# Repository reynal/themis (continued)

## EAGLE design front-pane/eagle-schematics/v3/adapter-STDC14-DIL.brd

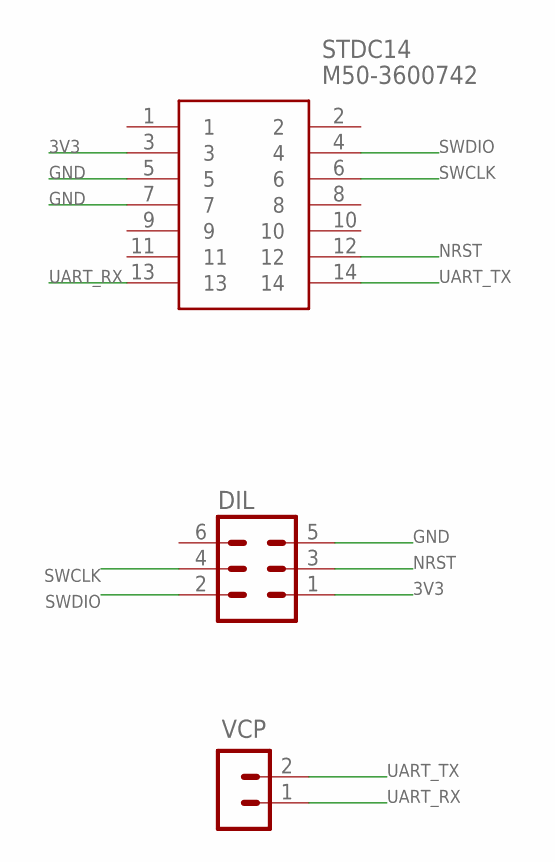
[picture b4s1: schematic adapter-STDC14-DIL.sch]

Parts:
DIL: MA03-2
STDC14: M50-3600742
VCP: MA02-1

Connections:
3V3: DIL.1, STDC14.3
GND: DIL.5, STDC14.5, STDC14.7
NRST: DIL.3, STDC14.12
SWCLK: DIL.4, STDC14.6
SWDIO: DIL.2, STDC14.4
UART_RX: STDC14.13, VCP.1
UART_TX: STDC14.14, VCP.2

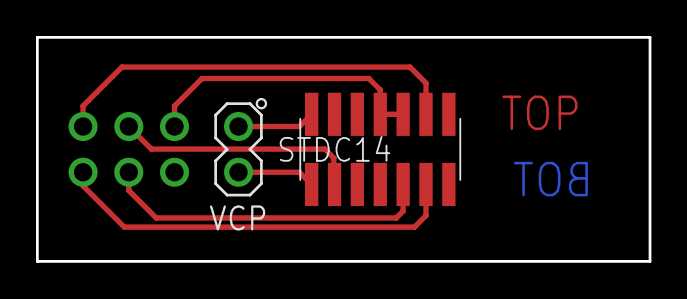
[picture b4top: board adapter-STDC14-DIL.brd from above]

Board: 2 copper layers, 34.0 x 12.4 mm, 3 parts (1 on the bottom side), 7 nets.

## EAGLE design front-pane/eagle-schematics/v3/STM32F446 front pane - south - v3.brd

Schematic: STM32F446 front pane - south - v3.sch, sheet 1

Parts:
C1, C4: 100n; 0805-CAP
C2, C3: 10u; CPOL2917
C5, C6, C7, C8, C9, C10, C11, C12, C13, C14, C20, C21, C22, C23, C24, C25, C26, C27, C28, C29, C34, C35, C36, C37, C38, C39, C40, C41, C42, C43, C44: 10n; 0805-CAP
C15, C16, C17, C18, C19, C30, C31, C32, C33, C45, C46, C47, C48: 100n; 1206
CON_NORTH_BRD: MA10-2
D1, D2, D3, D4: CZXR-80RGB03-A; LED4-2.0-D8.0MM
IC1, IC2, IC3, IC4, IC5, IC6, IC7, IC8, IC9, IC10, IC11, IC12, IC13: NEOPIXEL-TLC59731DR; SOIC127P600X175-8N
MCP_000, MCP_001: MCP23017; SOIC-28
R1, R2, R3, R4: 1k; R0805
R5, R6, R7, R8, R9, R10, R11, R12, R13, R14, R30, R31, R32, R33, R34, R35, R36, R37, R38, R39, R55, R56, R57, R58, R59, R60, R61, R62, R63, R64, R65: 470; 1206
R15, R16, R17, R19, R20, R21, R23, R24, R25, R27, R28, R29, R40, R41, R42, R44, R45, R46, R48, R49, R50, R52, R53, R54, R66, R67, R68, R70, R71, R72, R74, R75, R76, R78, R79, R80, R81, R82, R83: 100; 1206
R18, R22, R26, R43, R47, R51, R69, R73, R77: 10k; 1206
S1, S2, S3, S4, S5, S6, S7, S8, S9: ENCODER-RGB-SWITCH-NO_NUT; ENCODER_LED_3
SW1, SW2, SW3, SW4: B3F-1000

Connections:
3V3: C1.1, C2.+, C3.+, C4.1, C15.1, C16.1, C17.1, C18.1, C19.1, C30.1, C31.1, C32.1, C33.1, C45.1, C46.1, C47.1, C48.1, CON_NORTH_BRD.2, CON_NORTH_BRD.4, D1.2 (+), D2.2 (+), D3.2 (+), D4.2 (+), IC1.8 (VCC), IC2.8 (VCC), IC3.8 (VCC), IC4.8 (VCC), IC5.8 (VCC), IC6.8 (VCC), IC7.8 (VCC), IC8.8 (VCC), IC9.8 (VCC), IC10.8 (VCC), IC11.8 (VCC), IC12.8 (VCC), IC13.8 (VCC), MCP_000.9 (VDD), MCP_001.9 (VDD), MCP_001.15 (A0), R1.2, R2.2, R3.2, R4.2, S1.5 (+), S2.5 (+), S3.5 (+), S4.5 (+), S5.5 (+), S6.5 (+), S7.5 (+), S8.5 (+), S9.5 (+); also elsewhere on the board
DATA_PIXEL11: IC4.5 (SDO), IC8.6 (SDI)
DATA_PIXEL12: IC1.5 (SDO), IC4.6 (SDI)
DATA_PIXEL13: IC1.6 (SDI), IC3.5 (SDO)
DATA_PIXEL14: IC2.5 (SDO), IC3.6 (SDI)
DATA_PIXEL21: IC7.6 (SDI), IC8.5 (SDO)
DATA_PIXEL22: IC6.6 (SDI), IC7.5 (SDO)
DATA_PIXEL23: IC5.6 (SDI), IC6.5 (SDO)
DATA_PIXEL24: IC5.5 (SDO), IC9.6 (SDI)
DATA_PIXEL32: IC12.5 (SDO), IC13.6 (SDI)
DATA_PIXEL33: IC11.5 (SDO), IC12.6 (SDI)
DATA_PIXEL34: IC10.5 (SDO), IC11.6 (SDI)
DATA_PIXEL35: IC9.5 (SDO), IC10.6 (SDI)
GND: C1.2, C2.-, C3.-, C4.2, C5.1, C6.1, C7.1, C8.1, C9.1, C10.1, C11.1, C12.2, C13.2, C14.2, C15.2, C16.2, C17.2, C18.2, C19.2, C20.1, C21.1, C22.1, C23.1, C24.1, C25.1, C26.1, C27.2, C28.2, C29.2, C30.2, C31.2, C32.2, C33.2, C34.1, C35.1, C36.1, C37.1, C38.1, C39.1, C40.1, C41.1, C42.2, C43.2, C44.2, C45.2, C46.2, C47.2, C48.2, CON_NORTH_BRD.1, IC1.4 (GND), IC2.4 (GND), IC3.4 (GND), IC4.4 (GND), IC5.4 (GND), IC6.4 (GND), IC7.4 (GND), IC8.4 (GND), IC9.4 (GND), IC10.4 (GND), IC11.4 (GND), IC12.4 (GND), IC13.4 (GND), MCP_000.10 (VSS), MCP_000.15 (A0), MCP_000.16 (A1), MCP_000.17 (A2), MCP_001.10 (VSS), MCP_001.16 (A1), MCP_001.17 (A2), R18.2, R22.2, R26.2, R43.2, R47.2, R51.2, R69.2, R73.2, R77.2, S1.C, S2.C, S3.C, S4.C, S5.C, S6.C, S7.C, S8.C, S9.C, SW1.1, SW1.2, SW2.1, SW2.2, SW3.1, SW3.2, SW4.1, SW4.2; also elsewhere on the board
GPA0_11: MCP_000.21 (GPA0), R32.1, S4.B
GPA0_12: MCP_001.21 (GPA0), R58.1, S7.B
GPA1_11: MCP_000.22 (GPA1), R31.1, S4.A
GPA1_12: MCP_001.22 (GPA1), R63.1, R69.1, S7.3 (SW)
GPA2_11: MCP_000.23 (GPA2), R37.1, R43.1, S4.3 (SW)
GPA2_12: MCP_001.23 (GPA2), R57.1, S7.A
GPA3_11: MCP_000.24 (GPA3), R33.1, S5.A
GPA3_12: MCP_001.24 (GPA3), R60.1, S8.B
GPA4_11: MCP_000.25 (GPA4), R34.1, S5.B
GPA4_12: MCP_001.25 (GPA4), R59.1, S8.A
GPA5_11: MCP_000.26 (GPA5), R38.1, R47.1, S5.3 (SW)
GPA5_12: MCP_001.26 (GPA5), R64.1, R73.1, S8.3 (SW)
GPA6_11: MCP_000.27 (GPA6), R14.1, R26.1, S3.3 (SW)
GPA6_12: MCP_001.27 (GPA6), R55.1, SW3.3, SW3.4
GPA7_11: MCP_000.28 (GPA7), R5.1, SW1.3, SW1.4
GPA7_12: MCP_001.28 (GPA7), R56.1, SW4.3, SW4.4
GPB0_11: MCP_000.1 (GPB0), R10.1, S3.A
GPB1_11: MCP_000.2 (GPB1), R11.1, S3.B
GPB1_12: MCP_001.2 (GPB1), R62.1, S9.B
GPB2_11: MCP_000.3 (GPB2), R8.1, S2.A
GPB2_12: MCP_001.3 (GPB2), R65.1, R77.1, S9.3 (SW)
GPB3_11: MCP_000.4 (GPB3), R9.1, S2.B
GPB3_12: MCP_001.4 (GPB3), R61.1, S9.A
GPB4_11: MCP_000.5 (GPB4), R13.1, R22.1, S2.3 (SW)
GPB4_12: MCP_001.5 (GPB4), R39.1, R51.1, S6.3 (SW)
GPB5_11: MCP_000.6 (GPB5), R12.1, R18.1, S1.3 (SW)
GPB5_12: MCP_001.6 (GPB5), R35.1, S6.A
GPB6_11: MCP_000.7 (GPB6), R6.1, S1.A
GPB6_12: MCP_001.7 (GPB6), R36.1, S6.B
GPB7_11: MCP_000.8 (GPB7), R7.1, S1.B
GPB7_12: MCP_001.8 (GPB7), R30.1, SW2.3, SW2.4
I2C2_SCL: CON_NORTH_BRD.20; also elsewhere on the board
I2C2_SDA: CON_NORTH_BRD.5; also elsewhere on the board
I2C3_SCL: CON_NORTH_BRD.12, MCP_000.12 (SCL), MCP_001.12 (SCL), R2.1, R4.1
I2C3_SDA: CON_NORTH_BRD.11, MCP_000.13 (SDA), MCP_001.13 (SDA), R1.1, R3.1
INTA_2: CON_NORTH_BRD.13; also elsewhere on the board
INTA_11: CON_NORTH_BRD.8, MCP_000.20 (INTA)
INTA_12: CON_NORTH_BRD.9, MCP_001.20 (INTA)
INTA_31: CON_NORTH_BRD.18; also elsewhere on the board
INTA_32: CON_NORTH_BRD.15; also elsewhere on the board
INTB_2: CON_NORTH_BRD.14; also elsewhere on the board
INTB_11: CON_NORTH_BRD.7, MCP_000.19 (INTB)
INTB_12: CON_NORTH_BRD.10, MCP_001.19 (INTB)
INTB_31: CON_NORTH_BRD.17; also elsewhere on the board
INTB_32: CON_NORTH_BRD.16; also elsewhere on the board
unnamed: IC12.1 (OUT0), R81.1
unnamed: IC12.2 (OUT1), R82.1
unnamed: R23.2, S3.1 (-R)
unnamed: R24.2, S3.2 (-G)
unnamed: R25.2, S3.4 (-B)
unnamed: IC4.1 (OUT0), R23.1
unnamed: IC4.2 (OUT1), R24.1
unnamed: IC4.3 (OUT2), R25.1
unnamed: C10.2, R10.2
unnamed: C11.2, R11.2
unnamed: C14.1, R14.2
unnamed: R19.2, S2.1 (-R)
unnamed: R20.2, S2.2 (-G)
unnamed: R21.2, S2.4 (-B)
unnamed: IC3.1 (OUT0), R19.1
unnamed: IC3.2 (OUT1), R20.1
unnamed: IC3.3 (OUT2), R21.1
unnamed: C8.2, R8.2
unnamed: C9.2, R9.2
unnamed: C13.1, R13.2
unnamed: R15.2, S1.1 (-R)
unnamed: R16.2, S1.2 (-G)
unnamed: R17.2, S1.4 (-B)
unnamed: IC2.1 (OUT0), R15.1
unnamed: IC2.2 (OUT1), R16.1
unnamed: IC2.3 (OUT2), R17.1
unnamed: C6.2, R6.2
unnamed: C7.2, R7.2
unnamed: C12.1, R12.2
unnamed: IC12.3 (OUT2), R83.1
unnamed: C35.2, R56.2
unnamed: D4.1 (R), R83.2
unnamed: D4.4 (B), R82.2
unnamed: D4.3 (G), R81.2
unnamed: IC1.1 (OUT0), R27.1
unnamed: IC1.2 (OUT1), R28.1
unnamed: IC1.3 (OUT2), R29.1
unnamed: C5.2, R5.2
unnamed: R48.2, S6.1 (-R)
unnamed: R49.2, S6.2 (-G)
unnamed: R50.2, S6.4 (-B)
unnamed: IC8.1 (OUT0), R48.1
unnamed: IC8.2 (OUT1), R49.1
unnamed: IC8.3 (OUT2), R50.1
unnamed: C25.2, R35.2
unnamed: C26.2, R36.2
unnamed: C29.1, R39.2
unnamed: D1.1 (R), R29.2
unnamed: D1.4 (B), R28.2
unnamed: D1.3 (G), R27.2
unnamed: R44.2, S5.1 (-R)
unnamed: R45.2, S5.2 (-G)
unnamed: R46.2, S5.4 (-B)
unnamed: IC6.1 (OUT0), R44.1
unnamed: IC6.2 (OUT1), R45.1
unnamed: IC6.3 (OUT2), R46.1
unnamed: C23.2, R33.2
unnamed: C24.2, R34.2
unnamed: C28.1, R38.2
unnamed: IC7.1 (OUT0), R52.1
unnamed: IC7.2 (OUT1), R53.1
unnamed: IC7.3 (OUT2), R54.1
unnamed: C20.2, R30.2
unnamed: D2.1 (R), R54.2
unnamed: D2.4 (B), R53.2
unnamed: D2.3 (G), R52.2
unnamed: R40.2, S4.1 (-R)
unnamed: R41.2, S4.2 (-G)
unnamed: R42.2, S4.4 (-B)
unnamed: IC5.1 (OUT0), R40.1
unnamed: IC5.2 (OUT1), R41.1
unnamed: IC5.3 (OUT2), R42.1
unnamed: C21.2, R31.2
unnamed: C22.2, R32.2
unnamed: C27.1, R37.2
unnamed: R74.2, S9.1 (-R)
unnamed: R75.2, S9.2 (-G)
unnamed: R76.2, S9.4 (-B)
unnamed: IC13.1 (OUT0), R74.1
unnamed: IC13.2 (OUT1), R75.1
unnamed: IC13.3 (OUT2), R76.1
unnamed: C40.2, R61.2
unnamed: C41.2, R62.2
unnamed: C44.1, R65.2
unnamed: IC11.1 (OUT0), R78.1
unnamed: IC11.2 (OUT1), R79.1
unnamed: IC11.3 (OUT2), R80.1
unnamed: C34.2, R55.2
unnamed: D3.1 (R), R80.2
unnamed: D3.4 (B), R79.2
unnamed: D3.3 (G), R78.2
unnamed: R70.2, S8.1 (-R)
unnamed: R71.2, S8.2 (-G)
unnamed: R72.2, S8.4 (-B)
unnamed: IC10.1 (OUT0), R70.1
unnamed: IC10.2 (OUT1), R71.1
unnamed: IC10.3 (OUT2), R72.1
unnamed: C38.2, R59.2
unnamed: C39.2, R60.2
unnamed: C43.1, R64.2
unnamed: R66.2, S7.1 (-R)
unnamed: R67.2, S7.2 (-G)
unnamed: R68.2, S7.4 (-B)
unnamed: IC9.1 (OUT0), R66.1
unnamed: IC9.2 (OUT1), R67.1
unnamed: IC9.3 (OUT2), R68.1
unnamed: C36.2, R57.2
unnamed: C37.2, R58.2
unnamed: C42.1, R63.2
PIXEL42: IC2.6 (SDI); also elsewhere on the board
RST: CON_NORTH_BRD.3, MCP_000.18 (!RESET), MCP_001.18 (!RESET); also elsewhere on the board
SPI1_MOSI: CON_NORTH_BRD.6; also elsewhere on the board
SPI3_MOSI: CON_NORTH_BRD.19; also elsewhere on the board

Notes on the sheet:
RGB ENCODER 11
RGB ENCODER 13
RGB ENCODER 14
RGB ENCODER 21
RGB ENCODER 23
RGB ENCODER 24
RGB ENCODER 31
RGB ENCODER 34
RGB ENCODER 35
OSCILLATORS
SWITCH RGB 12
SWITCH RGB 22
SWITCH RGB 33
SWITCH RGB 32
MCP 11 & 12

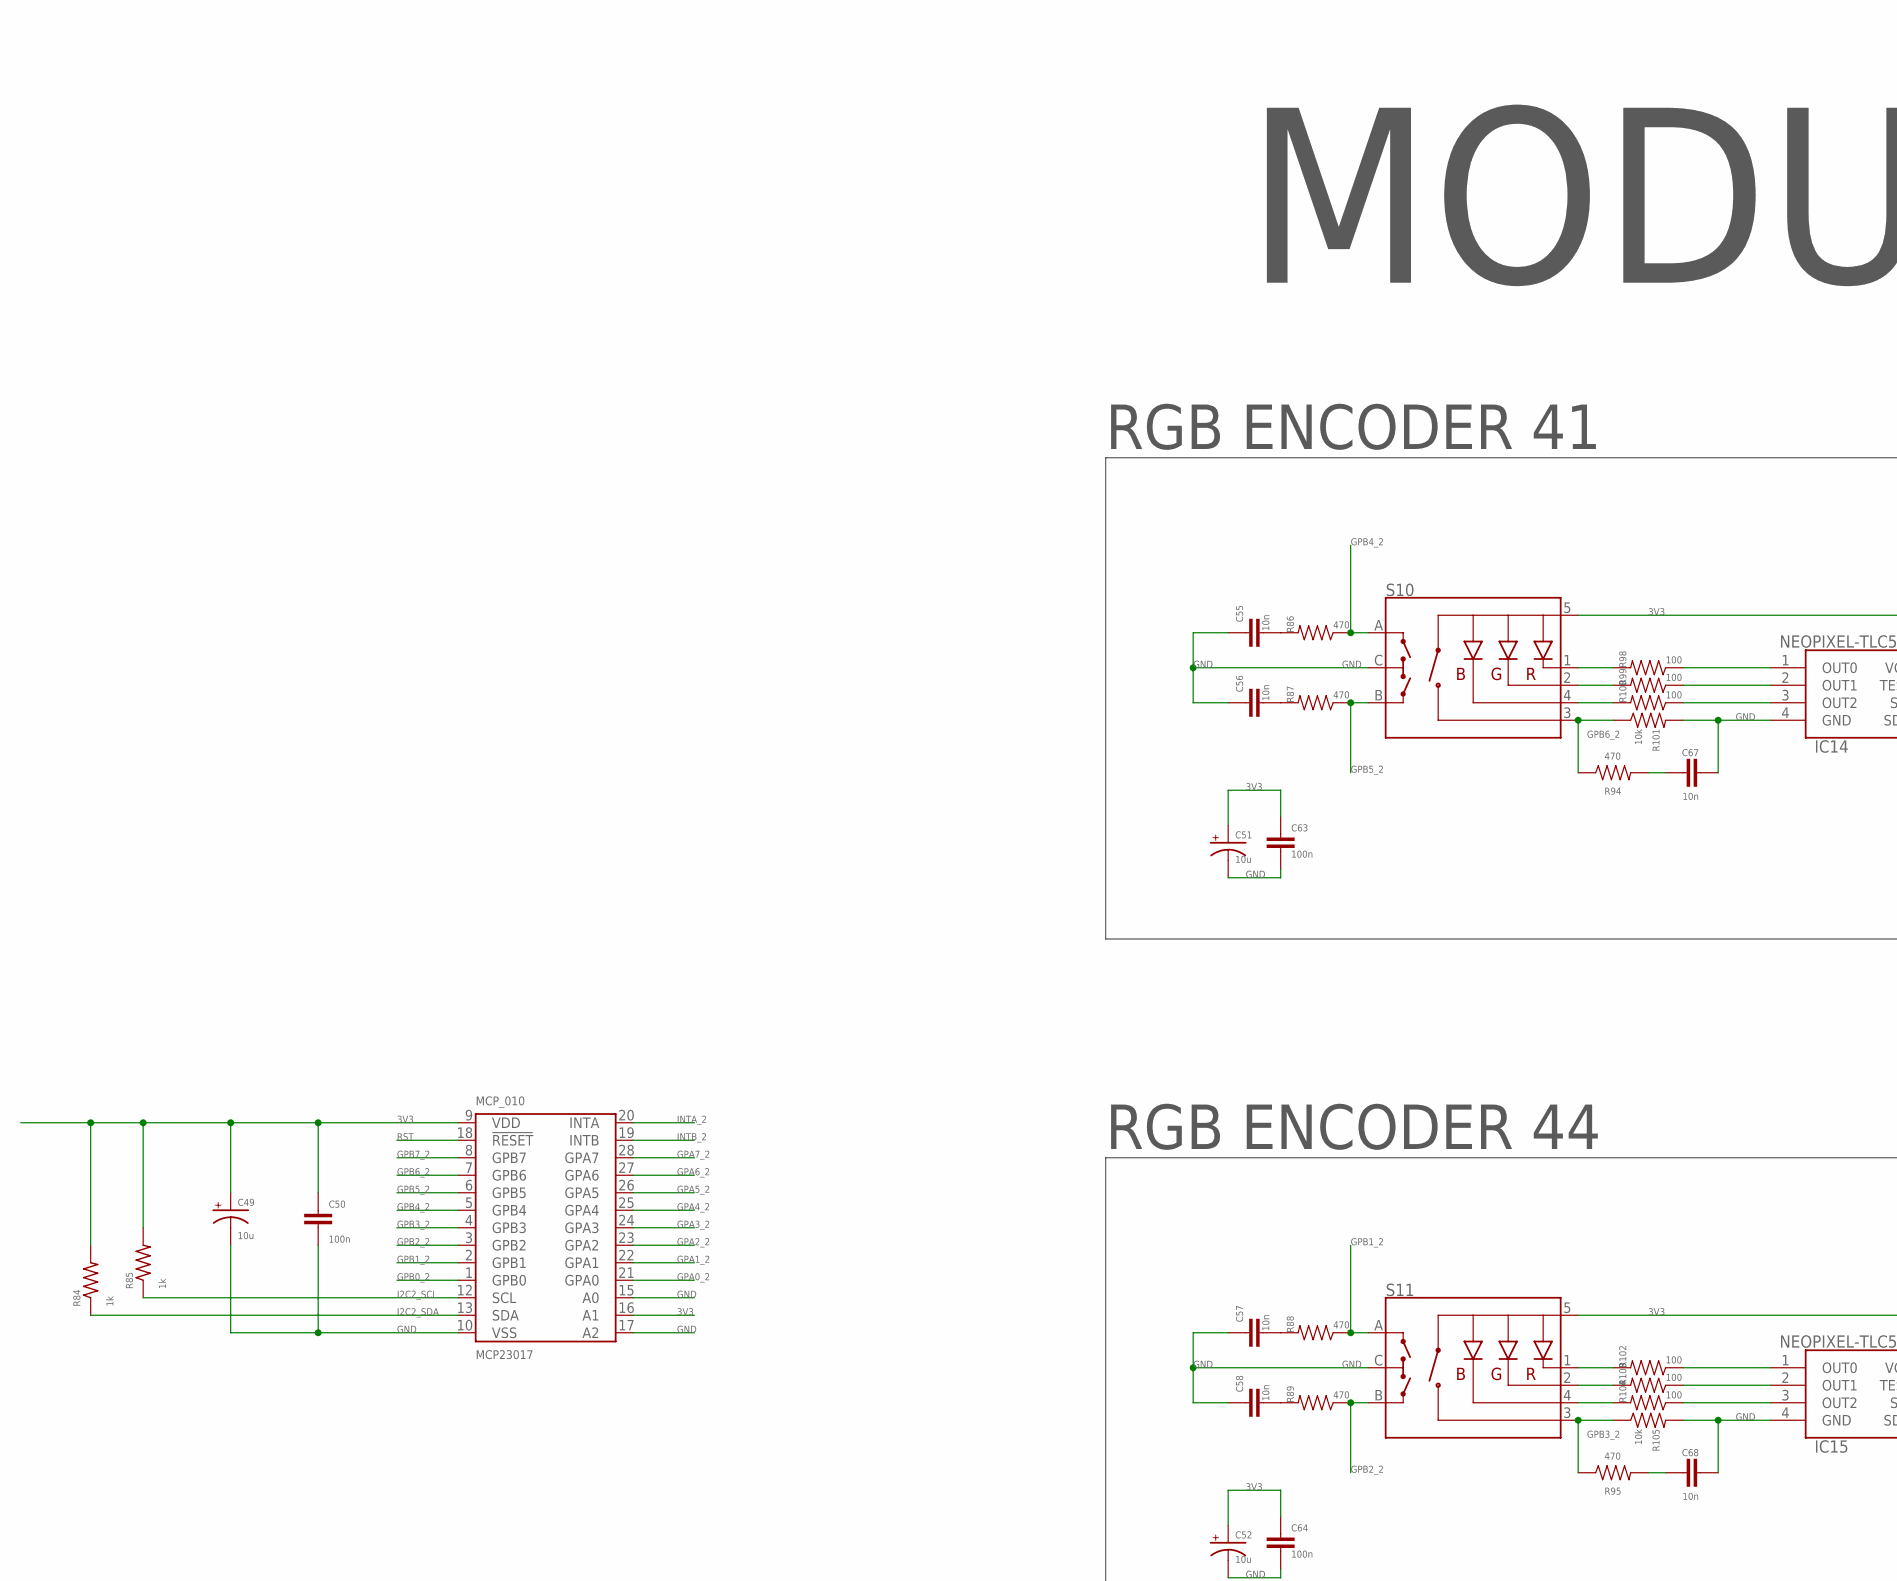
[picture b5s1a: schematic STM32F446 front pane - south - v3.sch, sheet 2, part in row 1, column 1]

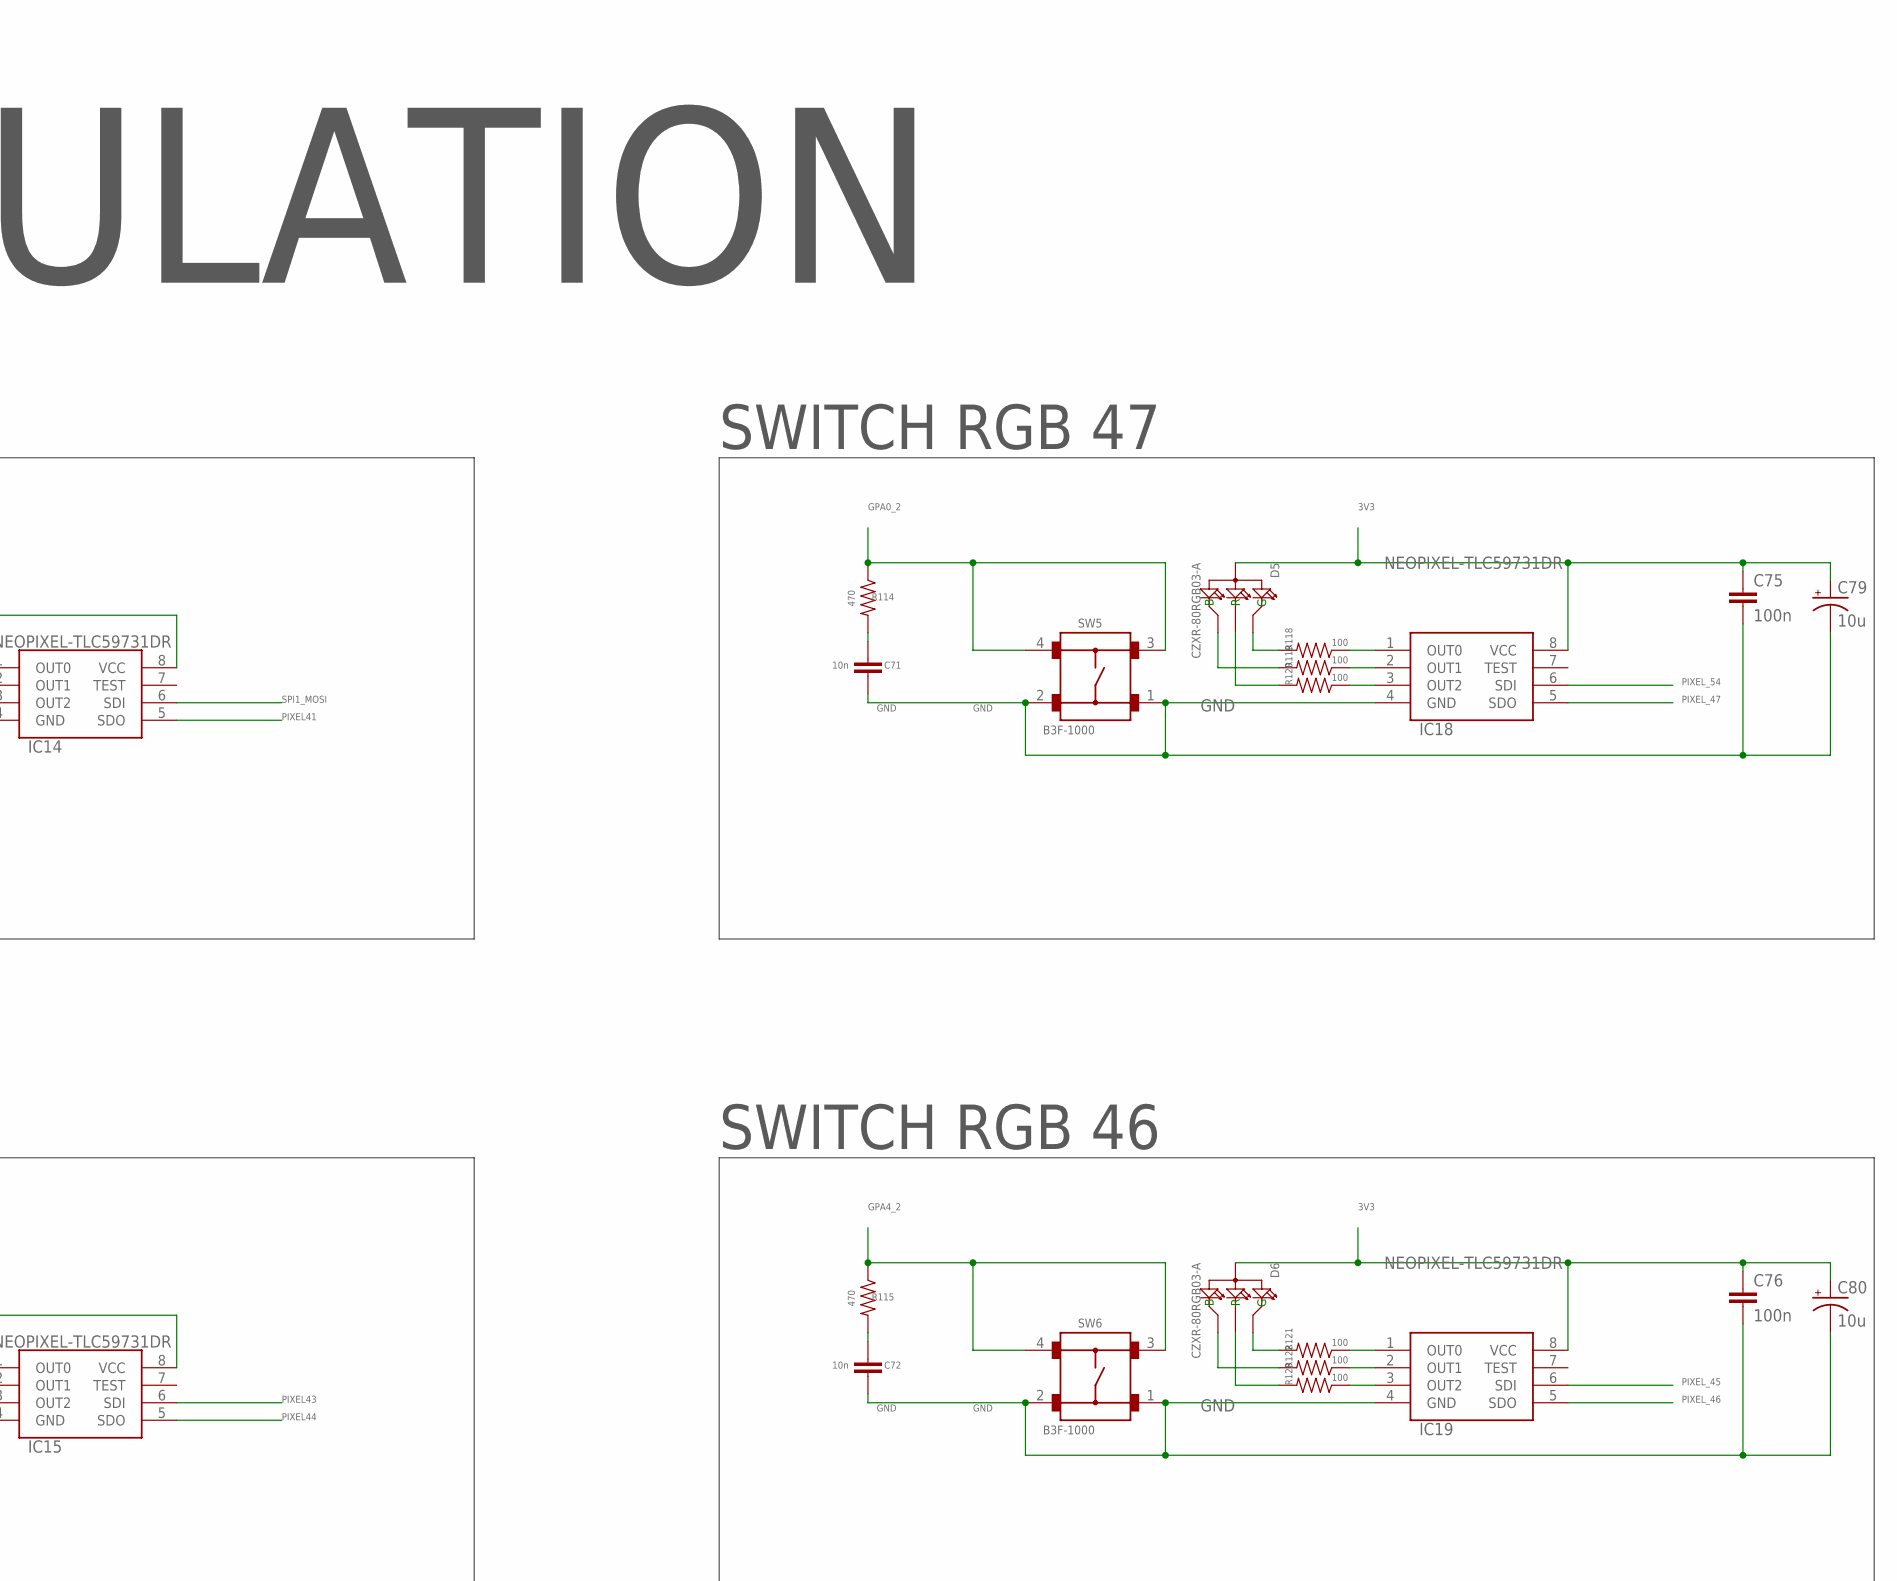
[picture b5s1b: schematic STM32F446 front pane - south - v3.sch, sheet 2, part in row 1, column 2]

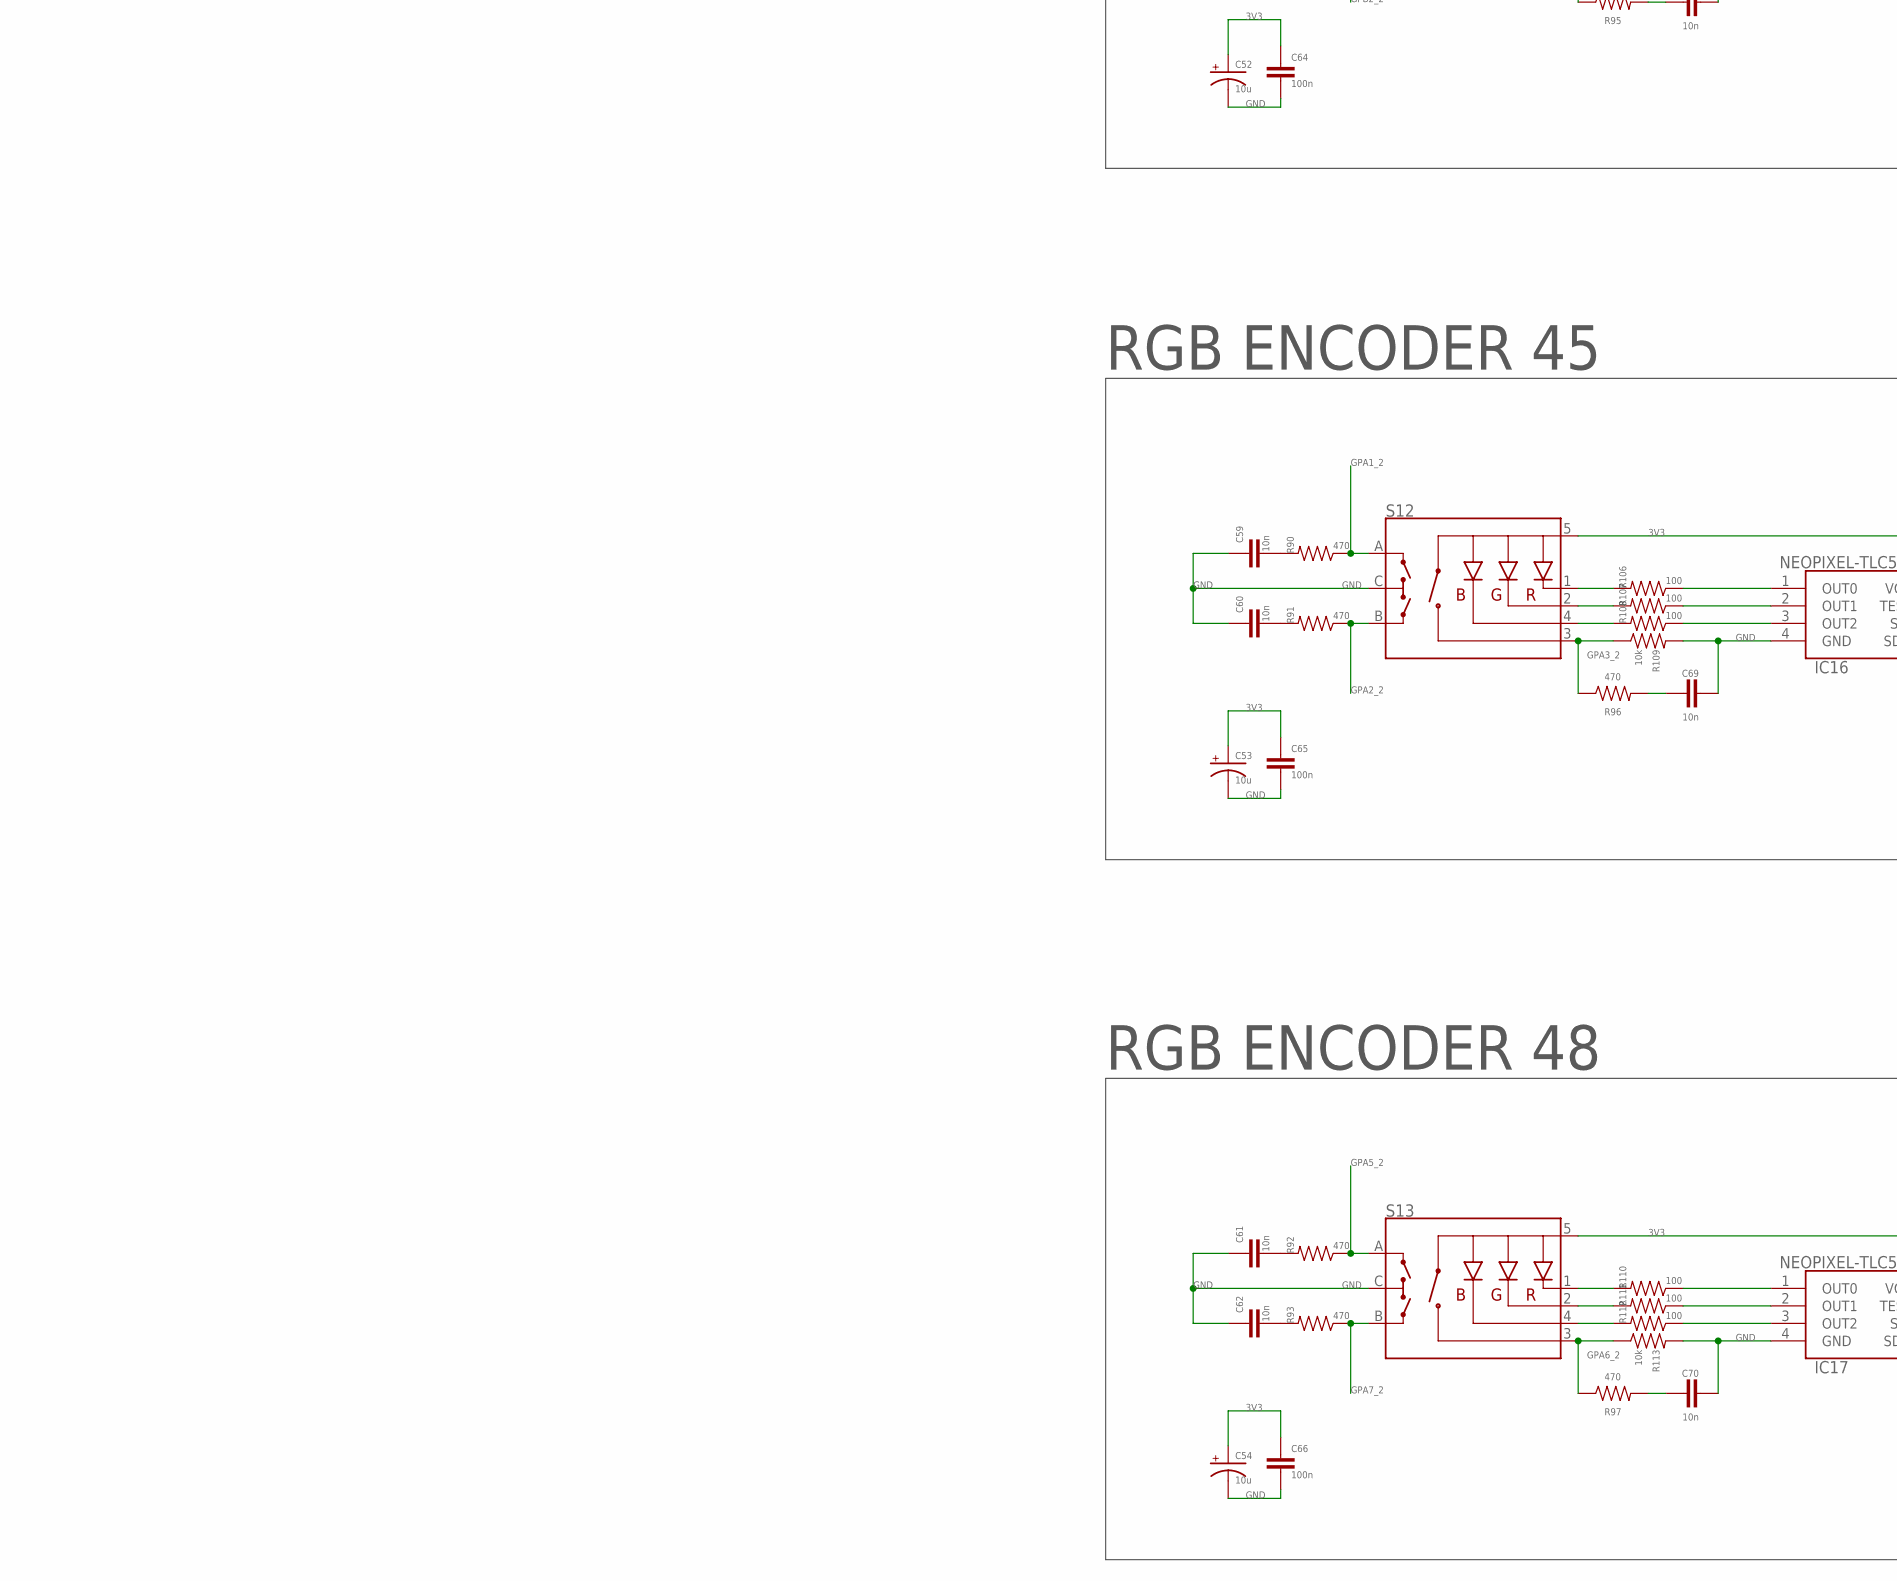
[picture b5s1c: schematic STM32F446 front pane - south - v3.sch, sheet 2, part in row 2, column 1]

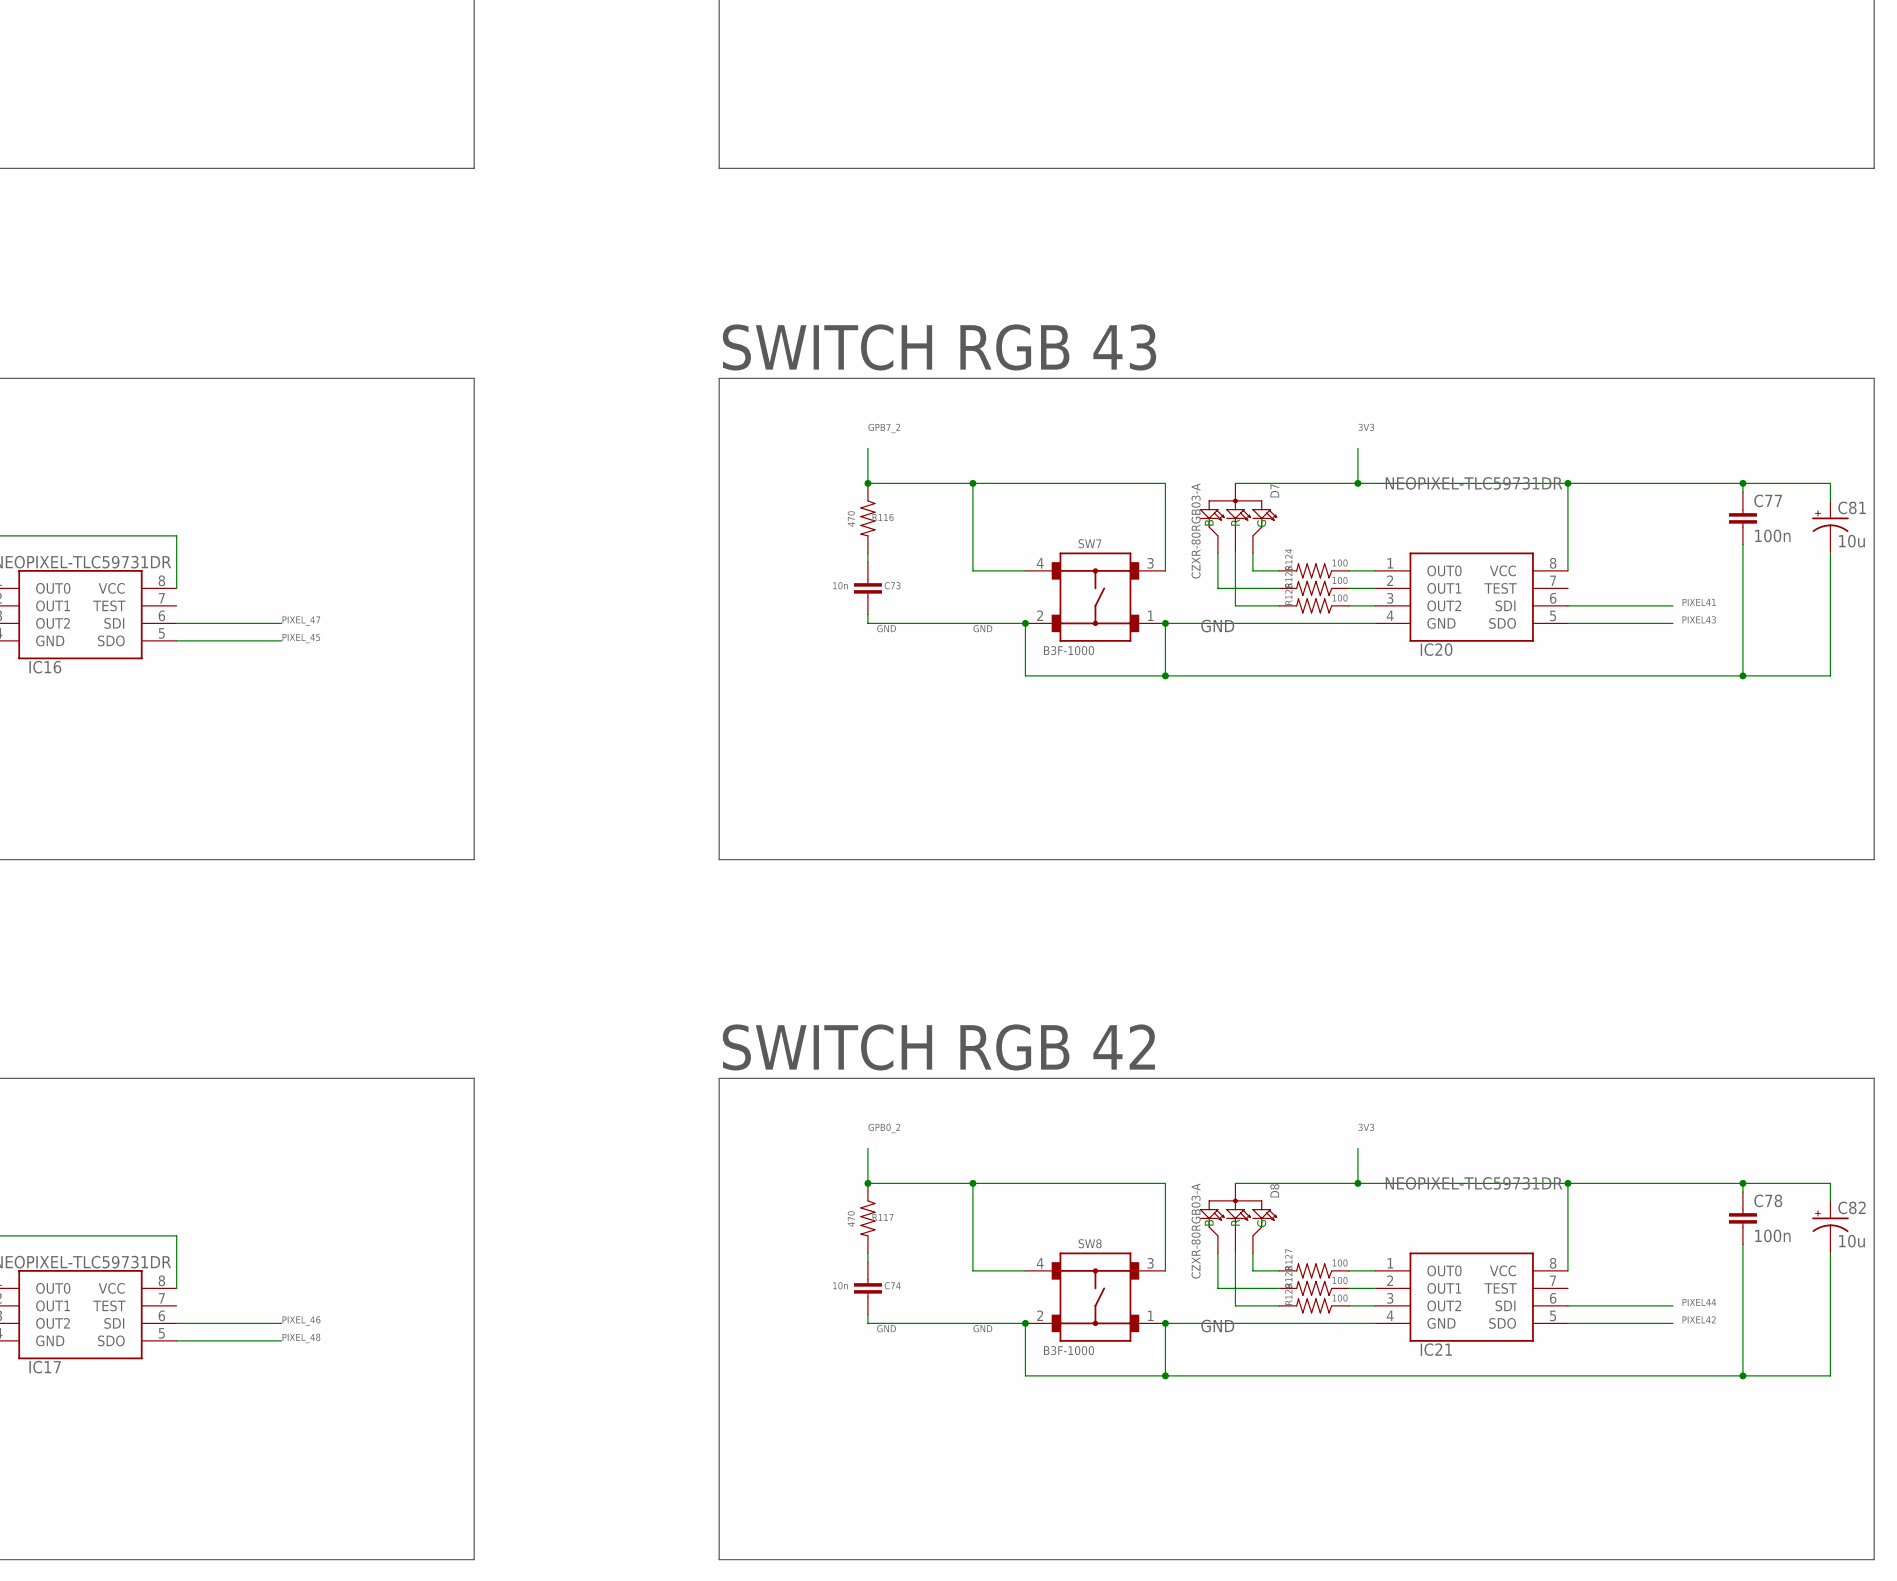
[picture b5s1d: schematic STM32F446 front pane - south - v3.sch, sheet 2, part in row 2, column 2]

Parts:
C49, C51, C52, C53, C54, C79, C80, C81, C82: 10u; CPOL2917
C50, C63, C64, C65, C66, C75, C76, C77, C78: 100n; 0805-CAP
C55, C56, C57, C58, C59, C60, C61, C62, C67, C68, C69, C70, C71, C72, C73, C74: 10n; 0805-CAP
D5, D6, D7, D8: CZXR-80RGB03-A; LED4-2.0-D8.0MM
IC14, IC15, IC16, IC17, IC18, IC19, IC20, IC21: NEOPIXEL-TLC59731DR; SOIC127P600X175-8N
MCP_010: MCP23017; SOIC-28
R84, R85: 1k; R0805
R86, R87, R88, R89, R90, R91, R92, R93, R94, R95, R96, R97, R114, R115, R116, R117: 470; 1206
R98, R99, R100, R102, R103, R104, R106, R107, R108, R110, R111, R112, R118, R119, R120, R121, R122, R123, R124, R125, R126, R127, R128, R129: 100; 1206
R101, R105, R109, R113: 10k; 1206
S10, S11, S12, S13: ENCODER-RGB-SWITCH-NO_NUT; ENCODER_LED_3
SW5, SW6, SW7, SW8: B3F-1000

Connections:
3V3: C49.+, C50.1, C51.+, C52.+, C53.+, C54.+, C63.1, C64.1, C65.1, C66.1, C75.1, C76.1, C77.1, C78.1, C79.+, C80.+, C81.+, C82.+, D5.2 (+), D6.2 (+), D7.2 (+), D8.2 (+), IC14.8 (VCC), IC15.8 (VCC), IC16.8 (VCC), IC17.8 (VCC), IC18.8 (VCC), IC19.8 (VCC), IC20.8 (VCC), IC21.8 (VCC), MCP_010.9 (VDD), MCP_010.16 (A1), R84.2, R85.2, S10.5 (+), S11.5 (+), S12.5 (+), S13.5 (+); also elsewhere on the board
GND: C49.-, C50.2, C51.-, C52.-, C53.-, C54.-, C55.1, C56.1, C57.1, C58.1, C59.1, C60.1, C61.1, C62.1, C63.2, C64.2, C65.2, C66.2, C67.2, C68.2, C69.2, C70.2, C71.1, C72.1, C73.1, C74.1, C75.2, C76.2, C77.2, C78.2, C79.-, C80.-, C81.-, C82.-, IC14.4 (GND), IC15.4 (GND), IC16.4 (GND), IC17.4 (GND), IC18.4 (GND), IC19.4 (GND), IC20.4 (GND), IC21.4 (GND), MCP_010.10 (VSS), MCP_010.15 (A0), MCP_010.17 (A2), R101.2, R105.2, R109.2, R113.2, S10.C, S11.C, S12.C, S13.C, SW5.1, SW5.2, SW6.1, SW6.2, SW7.1, SW7.2, SW8.1, SW8.2; also elsewhere on the board
GPA0_2: MCP_010.21 (GPA0), R114.1, SW5.3, SW5.4
GPA1_2: MCP_010.22 (GPA1), R90.1, S12.A
GPA2_2: MCP_010.23 (GPA2), R91.1, S12.B
GPA3_2: MCP_010.24 (GPA3), R96.1, R109.1, S12.3 (SW)
GPA4_2: MCP_010.25 (GPA4), R115.1, SW6.3, SW6.4
GPA5_2: MCP_010.26 (GPA5), R92.1, S13.A
GPA6_2: MCP_010.27 (GPA6), R97.1, R113.1, S13.3 (SW)
GPA7_2: MCP_010.28 (GPA7), R93.1, S13.B
GPB0_2: MCP_010.1 (GPB0), R117.1, SW8.3, SW8.4
GPB1_2: MCP_010.2 (GPB1), R88.1, S11.A
GPB2_2: MCP_010.3 (GPB2), R89.1, S11.B
GPB3_2: MCP_010.4 (GPB3), R95.1, R105.1, S11.3 (SW)
GPB4_2: MCP_010.5 (GPB4), R86.1, S10.A
GPB5_2: MCP_010.6 (GPB5), R87.1, S10.B
GPB6_2: MCP_010.7 (GPB6), R94.1, R101.1, S10.3 (SW)
GPB7_2: MCP_010.8 (GPB7), R116.1, SW7.3, SW7.4
I2C2_SCL: MCP_010.12 (SCL), R85.1; also elsewhere on the board
I2C2_SDA: MCP_010.13 (SDA), R84.1; also elsewhere on the board
INTA_2: MCP_010.20 (INTA); also elsewhere on the board
INTB_2: MCP_010.19 (INTB); also elsewhere on the board
unnamed: IC21.1 (OUT0), R127.1
unnamed: IC21.2 (OUT1), R128.1
unnamed: R98.2, S10.1 (-R)
unnamed: R99.2, S10.2 (-G)
unnamed: R100.2, S10.4 (-B)
unnamed: IC14.1 (OUT0), R98.1
unnamed: IC14.2 (OUT1), R99.1
unnamed: IC14.3 (OUT2), R100.1
unnamed: C55.2, R86.2
unnamed: C56.2, R87.2
unnamed: C67.1, R94.2
unnamed: R102.2, S11.1 (-R)
unnamed: R103.2, S11.2 (-G)
unnamed: R104.2, S11.4 (-B)
unnamed: IC15.1 (OUT0), R102.1
unnamed: IC15.2 (OUT1), R103.1
unnamed: IC15.3 (OUT2), R104.1
unnamed: C57.2, R88.2
unnamed: C58.2, R89.2
unnamed: C68.1, R95.2
unnamed: R106.2, S12.1 (-R)
unnamed: R107.2, S12.2 (-G)
unnamed: R108.2, S12.4 (-B)
unnamed: IC16.1 (OUT0), R106.1
unnamed: IC16.2 (OUT1), R107.1
unnamed: IC16.3 (OUT2), R108.1
unnamed: C59.2, R90.2
unnamed: C60.2, R91.2
unnamed: C69.1, R96.2
unnamed: R110.2, S13.1 (-R)
unnamed: R111.2, S13.2 (-G)
unnamed: R112.2, S13.4 (-B)
unnamed: IC17.1 (OUT0), R110.1
unnamed: IC17.2 (OUT1), R111.1
unnamed: IC17.3 (OUT2), R112.1
unnamed: C61.2, R92.2
unnamed: C62.2, R93.2
unnamed: C70.1, R97.2
unnamed: IC21.3 (OUT2), R129.1
unnamed: C74.2, R117.2
unnamed: D8.1 (R), R129.2
unnamed: D8.4 (B), R128.2
unnamed: D8.3 (G), R127.2
unnamed: IC20.1 (OUT0), R124.1
unnamed: IC20.2 (OUT1), R125.1
unnamed: IC20.3 (OUT2), R126.1
unnamed: C73.2, R116.2
unnamed: D7.1 (R), R126.2
unnamed: D7.4 (B), R125.2
unnamed: D7.3 (G), R124.2
unnamed: IC19.1 (OUT0), R121.1
unnamed: IC19.2 (OUT1), R122.1
unnamed: IC19.3 (OUT2), R123.1
unnamed: C72.2, R115.2
unnamed: D6.1 (R), R123.2
unnamed: D6.4 (B), R122.2
unnamed: D6.3 (G), R121.2
unnamed: IC18.1 (OUT0), R118.1
unnamed: IC18.2 (OUT1), R119.1
unnamed: IC18.3 (OUT2), R120.1
unnamed: C71.2, R114.2
unnamed: D5.1 (R), R120.2
unnamed: D5.4 (B), R119.2
unnamed: D5.3 (G), R118.2
PIXEL41: IC14.5 (SDO), IC20.6 (SDI)
PIXEL42: IC21.5 (SDO); also elsewhere on the board
PIXEL43: IC15.6 (SDI), IC20.5 (SDO)
PIXEL44: IC15.5 (SDO), IC21.6 (SDI)
PIXEL_45: IC16.5 (SDO), IC19.6 (SDI)
PIXEL_46: IC17.6 (SDI), IC19.5 (SDO)
PIXEL_47: IC16.6 (SDI), IC18.5 (SDO)
PIXEL_48: IC17.5 (SDO); also elsewhere on the board
PIXEL_54: IC18.6 (SDI); also elsewhere on the board
RST: MCP_010.18 (!RESET); also elsewhere on the board
SPI1_MOSI: IC14.6 (SDI); also elsewhere on the board

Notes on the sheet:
MODULATION
RGB ENCODER 41
RGB ENCODER 44
RGB ENCODER 45
RGB ENCODER 48
SWITCH RGB 42
SWITCH RGB 43
SWITCH RGB 46
SWITCH RGB 47
